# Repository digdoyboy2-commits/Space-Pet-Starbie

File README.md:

Space-Pet-Starbie

A Starbie is an interactive pet powered by a XIAO ESP32-C3 microcontroller. It features an OLED display for expressions, an MPU6050 6-axis IMU for motion tracking, and a DHT11 sensor for temperature and humidity monitoring.

Features & Hardware
- MCU: XIAO ESP32-C3
- Display:OLED Display (SSD1306)
- Sensors: MPU6050 IMU & DHT11 Temp/Humidity Sensor
- Custom PCB Designed in KiCad
  I changed up the design and made my own theme.

Bill of Materials (BOM)

| Part | Quantity | Unit Price | Link |

Seeed Studio XIAO ESP32-C3 | 1 | $4.99 | [Link](https://www.seeedstudio.com/XIAO-ESP32C3-p-5432.html) |
SSD1306 OLED Display (0.96") | 1 | $3.50 | [Link](https://www.amazon.com) |
MPU6050 IMU Module | 1 | $2.50 | [Link](https://www.amazon.com) |
 DHT11 Temperature & Humidity Sensor | 1 | $1.50 | [Link](https://www.amazon.com) |
 Custom KiCad PCB | 1 | - | - |

Project Images

Project Images
  Schematic

  PCB Layout

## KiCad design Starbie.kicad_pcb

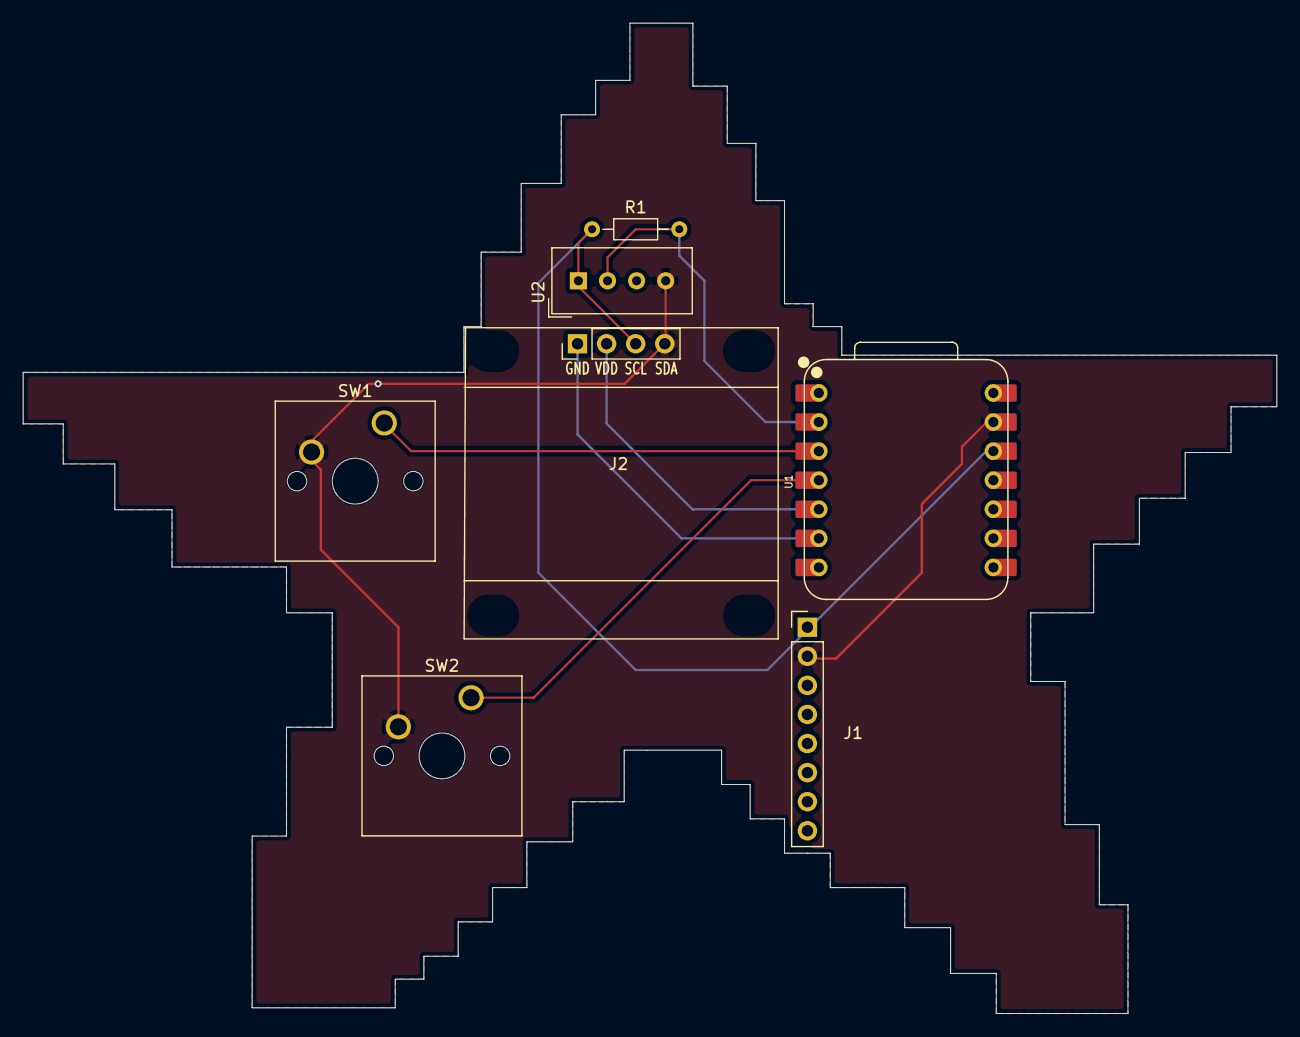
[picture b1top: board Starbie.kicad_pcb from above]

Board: 2 copper layers, 109.5 x 86.5 mm, 7 parts (0 on the bottom side), 7 nets.

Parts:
J1: Conn_01x08_Pin; PinHeader_1x08_P2.54mm_Vertical
J2: Conn_01x04_Pin; Display_128x64_096_I2C
R1: 10k; R_Axial_DIN0204_L3.6mm_D1.6mm_P7.62mm_Horizontal
SW1, SW2: SW_Push; SW_Cherry_MX_1.00u_PCB
U1: XIAO-ESP32-C3-SMD; XIAO-ESP32-C6-DIP
U2: DHT11; Aosong_DHT11_5.5x12.0_P2.54mm

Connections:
+3.3V: J1.1, J2.3, R1.1, U1.12 (3V3_OUT), U2.1 (VDD)
/DHT11 DATA: R1.2, U1.2 (D1), U2.2 (DATA)
/GPIO2: SW1.1, U1.3 (D2)
/GPIO3: SW2.1, U1.4 (D3)
/SCL: J2.2, U1.5 (D4)
/SDA: J2.1, U1.6 (D5)
GND: J1.2, J2.4, SW1.2, SW2.2, U1.13 (GND), U2.4 (GND)
